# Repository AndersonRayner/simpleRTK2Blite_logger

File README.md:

# SimpleRTK2Blite Logger Board
A simple logging board for the simpleRTK2BLite board from ArduSimple.  Uses COTS components to make assembly quick and easy.

Make sure to clone recursively!
```
https://github.com/AndersonRayner/simpleRTK2Blite_logger.git --recursive
```

Features:
- 5-36 V Input (XT30 Connector) 
- Logging to SD Card

## Hardware
Design files (KiCAD) are in the hardware folder.
Most parts are COTS
- simpleRTK2blite board | https://www.ardusimple.com/simplertk2blite/
- SparkFun OpenLog | https://www.sparkfun.com/products/13712
- Pololu 3V3 Regulator | https://www.pololu.com/product/2842
- XBee Radio v3
  - PCB Antenna | https://www.sparkfun.com/products/15126
  - External Antenna | https://www.sparkfun.com/products/15131 
- Custom PCB | See the hardware folder

## Software
Various scripts for generating post-processed solutions and extracting NMEA data.

### Configuration Files
Configuration files for the Base and Rover. 

## Notes
### GPS Accuracy vs. Decimal Places
| Decimals | Degrees    | Distance |
|----------|------------|----------|
| 0        | 1.0        | 111 km   |
| 1        | 0.1        | 11.1 km  |
| 2        | 0.01       | 1.11 km  |
| 3        | 0.001      | 111 m    |
| 4        | 0.0001     | 11.1 m   |
| 5        | 0.00001    | 1.11 m   |
| 6        | 0.000001   | 0.111 m  |
| 7        | 0.0000001  | 1.11 cm  |
| 8        | 0.00000001 | 1.11 mm  |

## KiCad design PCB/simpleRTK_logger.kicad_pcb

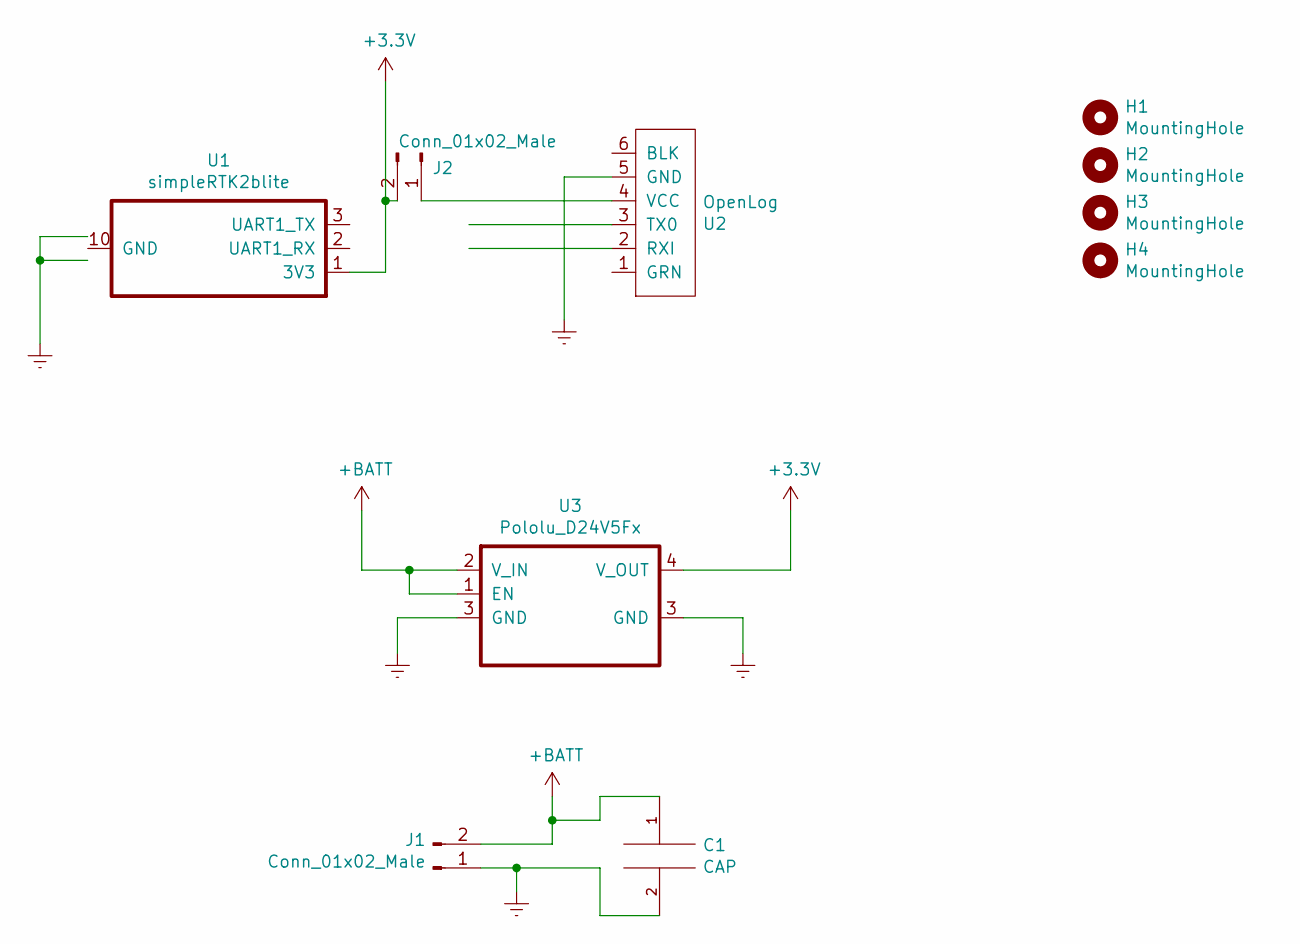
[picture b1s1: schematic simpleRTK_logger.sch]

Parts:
C1: CAP; PinHeader_1x02_P2.54mm_Vertical
H1, H2, H3, H4: MountingHole; MountingHole_2.2mm_M2
J1: Conn_01x02_Male; AMASS_XT30PW-M_1x02_P2.50mm_Horizontal
J2: Conn_01x02_Male; PinHeader_1x02_P2.54mm_Vertical
U1: simpleRTK2blite; simpleRTK2blite_THT
U2: OpenLog
U3: Pololu_D24V5Fx; Pololu_D24V5Fx_THT

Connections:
+3V3: J2.2, U1.1 (3V3), U3.4 (V_OUT)
+BATT: C1.1, J1.2, U3.1 (EN), U3.2 (V_IN)
Earth: C1.2, J1.1, U1.10 (GND), U1.11, U2.5 (GND), U3.3 (GND)
unnamed: J2.1, U2.4 (VCC)

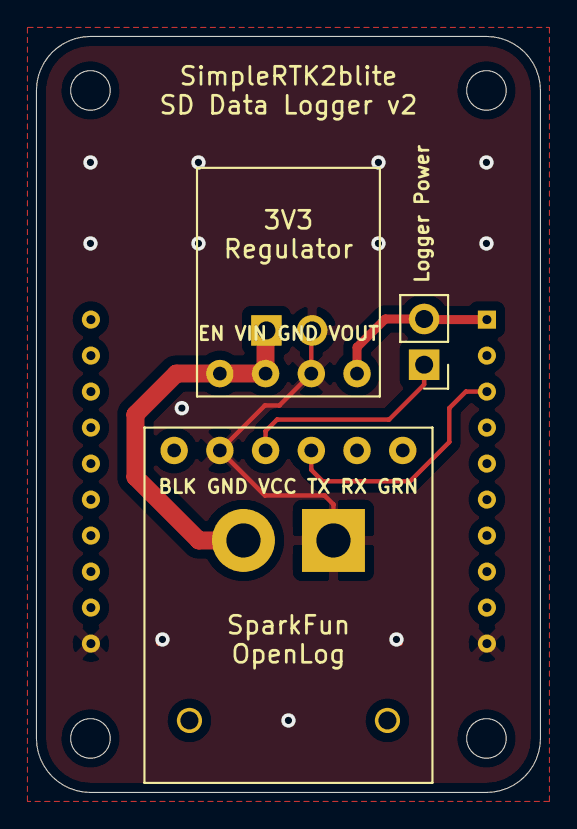
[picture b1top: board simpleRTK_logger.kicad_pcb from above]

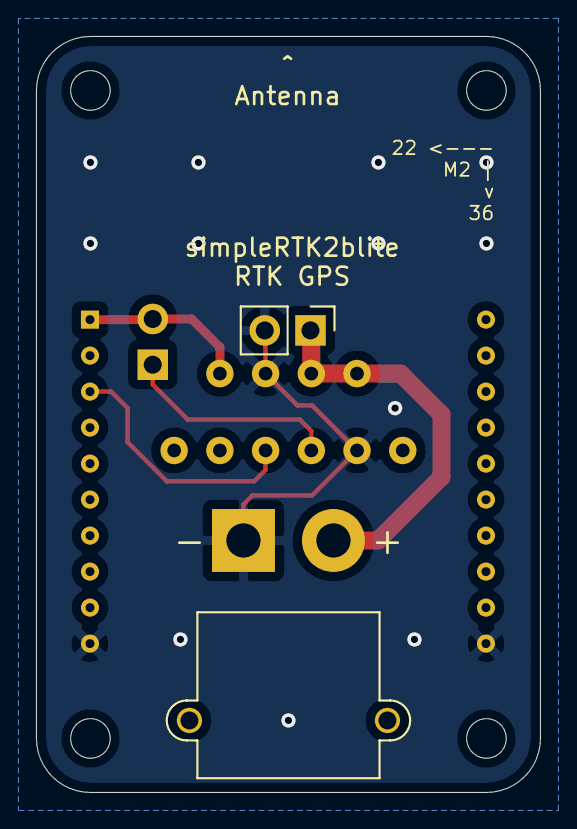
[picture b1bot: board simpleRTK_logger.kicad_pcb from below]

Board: 2 copper layers, 28.0 x 42.0 mm, 10 parts (3 on the bottom side), 4 nets.

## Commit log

2021-05-06 Lots of stuff
2021-05-12 Working on fixing the processing code
2021-05-31 Readme file
2021-12-29 Adding submodule and fixing stuff
2021-12-29 Submodule update
2022-12-09 Rename NOTES.md to README.md
2022-12-09 Added open logger configuration file
